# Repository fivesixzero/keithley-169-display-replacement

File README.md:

# Keithley 169 Multimeter Display Replacement

KiCad files, images, and documentation for replacing the Keithley 169's original LCD panel.

Also includes selected historical data including ad clippings and datasheets about the circa 1979 Keithley 169 digital multimeter and the Intersil ICL-7106R chip its built around.

## Overview

Many aging Keithley 169 multimeters have displays that are broken or flooded with liquid crystal. Because of this, they end up being thrown away or are left to be used for parts. This makes me sad.

The the main purpose of this project is to replace the Keithley 169's 'unobtanium' custom LCD display part with something inexpensive and (ideally) widely available as of mid-2021. Even if the part(s) selected in this project are unavailable in the future, or if more appropriate parts become available, this project should provide a solid starting point for future related work.

The secondary objective of this project is to provide an excuse to learn KiCad and do some historical digging about late 1970's digital multimeters, with a focus on multimeters based on the ICL7106 and its various variants.

## What's In This Repo?

The KiCad files for the board's schematic, PCB layout, symbols, and part footprints along with manufacturing output Gerber files are in `board`.

Key part datasheets and other historical data, along with images from my own build, are under `images`.

## Historical Context

### Digital Multimeters in the 70's

Largely due to the cost, DMMs were pretty exotic tech, despite having been around since the mid 1950's. The benefits the DMM over the analog meter were vast though.

Portability was becoming a larger concern too, now that it wasn't just "men of science" in lab coats, factory workers on an assembly line, or military signals specialists that needed to keep an eye on electronics. Tradespeople like electricians, auto mechanics, and service techs repairing millions of TVs, radios, and appliances all needed a reliable tool for their work. Adding to this was a rapidly growing consumer market driven by DIY tinkers, auto enthusiasts, HAM and CB radio folks, and those weird "computer clubs" popping up in California and Texas and, by the late 70's, all over the place.

A few smart players, including leadership at the John Fluke Company, saw an opportunity and a potentially huge addressable market. The key barrier to breaking into and expanding this market was price. Sure, equipment had to be rugged, reliable, and accurate, but those were comparatively easy problems to solve. But at the end of the day, DMMs were an order of magnitude too costly.

### The Fluke 8020A

As the story goes, in the mid-70's Fluke began a project with LSI specialists at Intersil. Their goal? To create an LSI device that could allow for the creation of a low-cost, portable, accurate, low-power-draw digital multimeter. When Fluke/Intersil started their work DMMs were very much out of the reach of average people and even most tradespeople. Portable options existed but they were typically just heavy, bulky bench gear with handles that could be powered on for only a few hours on a single charge or set of disposable batteries. This project aimed to flip that on its head.

In mid 1977, the Fluke 8202A was born. The chip at the heart of the 8020A, the Fluke `429100`, was nothing short of revolutionary. It enabled the development of a futuristic device that could do everything most people needed and it was a fraction of the price at $169, or around $1050 in 2021-adjusted buying power. While this sounds expensive today it was a huge deal at the time and was arguably the first practical example of a whole new type of everyday tool - the handheld multimeter.

Not much later, in 1978, Intersil released their `ICL7106` and its LED-driving sibling the `ICL7107`. Word has it that when Fluke heard about this chip, their engineers picked one up and took a look under the hood, finding that it was the very same design they had worked on with Intersil - right down to a tiny Fluke logo on the circuit mask. In an apparent effort to differentiate the design, Intersil had masked over (removed) one key feature (an internal switch to increase the input voltage range form 200mV to 2V) but that wasn't enough to stop a lawsuit from Fluke.

### The Intersil `ICL7106`

Of course, given the close relationship and interdependency between the two companies that suit was short-lived and settled out of court. But the cat was out of the bag - the `ICL7106` was ready for prime time. By the end of 1978 the `7106` was being sold by electronics distributors in kit form for as little as $30, complete with a new high-tech LCD panel! All a hobbyist (or prototype developer) had to do was give it zero to 200mV and, boom, they could get a 3.5-digit readout.

The key innovation was the fact that the `ICL7106` combined two key things into a single package - a high quality, dual-slope ADC and a 7-segment decoder/display driver. Neither of two things were particularly new, but having them in a single package was a huge innovation. Two major, complex sub-circuits that used to require dozens of discrete components were almost entirely eliminated from the board!

### DMM Democratization

So it wasn't just hobbyists paying attention to this new chip. Just about every test gear maker had at least one `ICL710x` based product in the works by the end of 1978. All a designer had to do was make sure that an analog font-end could present the LSI with a properly conditioned/divided input voltage, add a few decent-quality capacitors and resistors, and wire up a display.

Before long every manufacturer of test equipment (and a few 'new' names) had portable DMMs on the market and prices plummeted. Only a few years before, an 3.5-digit DMM would've required an investment of $500+ and substantial real estate on a workbench. Now any engineer or tech could carry that capability in their pocket for under $200 with battery life measured in months and years.

By the middle of the 1980's decent quality DMMs could be found under $100 and, eventually, down into the $50 and lower price points that made them household items across the US. In the 90's, `ICL7106` successors, variants and clones brought prices down well under $10. And even today in 2021 you can still get `ICL7106`, its sibling chips like the `ICL7136` and `MAX130A`, and all kinds of pin-compatible clones from Digi-Key, Mouser, Farnell, TME, and dozens of AliExpress shops.

### Keithley in the 70's

Now lets go back to 1978. Looking in from the outside, it looks like Keithley's leadership saw an opportunity in the low-end market. Their expertise and reputation lay elsewhere, in building some of the highest-grade measurement gear in the world for government, institutions, and the most well-funded corporate R&D departments. But somewhere in the halls of Keithley's offices, it seems like someone took a look at the Fluke 8020A and said, "I bet we can do that better."

Keithley had been building DMMs for the workbench for awhile at this point. As early as 1972 they had the $325 (~$2100 in 2021) Keithley 167, a 3.5-digit 'handheld' probe that was basically a tiny LCD display on the back of a bulky probe with a thick cable running back to a brick of bench tool. Later that year, a similar device, the 190 came to market with a 5.5-digit Nixie display for only $750 - around $4000 in 2021 dollars.

By the end of 1976, Keithley had a low-end to mid-range lineup that included 3.5-digit DMMs like the LCD-display 168 ($315) and 165 ($495), the 160B, and the 616 along with 4.5-digit DMMs like the 172 ($499) and 173 ($625), 171, 174, and 180. On the high end they had the 190 5.5-digit DMM. At the very top end, they had the 5900 and 6900, with "accuracy, stability, and sensitivity measured in ppm" and (likely) astronomical cost to go with it.

As the market accelerated toward the end of the 70's and LCD displays fully replaced Nixies, Keithley seems to have committed fully to the 'low end' of the market. Their 1978 lineup of all-LCD-display models was as strong as any other test gear company at the time. The model 179 was an LCD-display 4.5 digit meter for only $199, albeit with a few limitations. The 179 added a few things now considered critical, like sensitive TRMS AC measurements, at $289. Their more feature rich sibling, the 177, was quite a bit more capable but came in at a much higher price of $389. Then there was the 5.5-digit 191 at $499, complete with 4-wire resistance measurement - the cream of the 1978 crop.

So while they were certainly making strong moves in the low-cost corners of the market, even getting as low as $200, these were pretty pricey compared to their contemporaries. Their most inexpensive models often came with undesirable limitations. Battery power was an expensive option or aftermarket feature that could only offer a few dozen hours of battery life at best. And, most importantly, the 8020A hadn't come out yet.

### The Keithley 169

Enter the model 169, at $149.

Based on contextual data, like the frequency of ads and periodicals targeted by those ads, it looks like the Keithley 169 was announced in mid 1979 and started becoming available in quantity toward the end of that same year. This puts it squarely in the first or second generation of affordable meters based on the `ICL7106` chip.

Like most of the other brand-new 3.5-digit multimeters of the era, its specs were pretty impressive at the price. To differentiate the 169 from the others in its class, Keithley appears to have differentiated this meter with three main points.

First, it was portable. Not 8020A-style handheld portable, but portable via a pretty well engineered handle on a case the size of a large encyclopedia book. More impressive was the 1 year of battery life on a fresh set of 6 "C" batteries, co-incidentally the recommend time between calibrations.

Second, it was rugged. They touted the ruggedized thermoplastic, heavy input protection (1400V!), an MTBF of "20,000 hrs. or about 10 years", and "extensive vibration stress testing".

Third, Keithley was proud of its user interface. The display was "60% larger than other DMMs". It featured auto-zero, auto-polarity, and "color-coded front panel" that, at least in Keithley's eyes, was superior to their competition.

But most importantly, the price was $149, $20 cheaper than Fluke's 8020A.

Like a lot of things from the late 70's though, the 169 didn't live very long. Advertisements for the 169 only appear to have been published during a small window - from August of 1979 to March of 1980, or as late as June 1980 if you count an ad shared with the 130.

So by the time the 80's really started the 169 was already obsolete. On the low-end the industry as a whole abandoned the 'bench box' form-factor the 169 came in, replacing it with shirt-pocket-portable models. For Keithley, this was 130 family with the 130 at $99-115, the 131 at $134, the bringing-the-beeps-back 128 at $139, and the fanciest one, the 4.5-digit 135 at $219.

In the familiar bench-box format, the 169 was as low as Keithley ever got. In 1981 the 176 4.5-digit LCD DMM came in at a respectable $269. And with that, by 1982, the 169 looks like it was well and truly dead, at least in terms of marketing.

### Okay, so why fix up a Keithley 169?

I don't really have a single good answer for that. In many ways, its kind of a short-lived runt of the very large litter of late-70's DMMs. Its not particularly interesting in terms of specs, design, or historical importance. Its just another `ICL7106` follow-on of the historic 8020A, right?

Maybe. But for me, what sets this meter apart from the others is the engineering knowledge that went into building a stable and accurate analog front-end while also massively driving down the overall cost by keeping the design as simple as possible.

More speculatively, its possible that the 169 was effectively a prototype of sorts for the much more portable (and apparently more successful) follow-ups like the 130, 128, 131, and 135.

Either way, it played a part in bringing higher-quality measurement to the masses. And that's something I'll always find appealing.

### References

* George Rostky via EETimes, "Gauging the impact of DVMs", <https://web.archive.org/web/20040518004613/https://www.eet.com/anniversary/designclassics/gauging.html>
* `drtaylor` via EEVBlog forums, "History of the Fluke 8020A", <https://web.archive.org/web/20210301172454/https://www.eevblog.com/forum/testgear/history-of-the-fluke-8020-series/>
* Fluke, "Multimeter History", <https://www.fluke.com/en-us/learn/blog/digital-multimeters/multimeter-history>
* FundingUniverse, "Keithley Instruments History", <http://www.fundinguniverse.com/company-histories/keithley-instruments-inc-history/>

## License Clarifications

The license outlined in the `LICENSE` file in this repo is only relevant for the board files under `board`, the images under `images/k169-sn-59894` and `images/board`, and any Markdown documentation.

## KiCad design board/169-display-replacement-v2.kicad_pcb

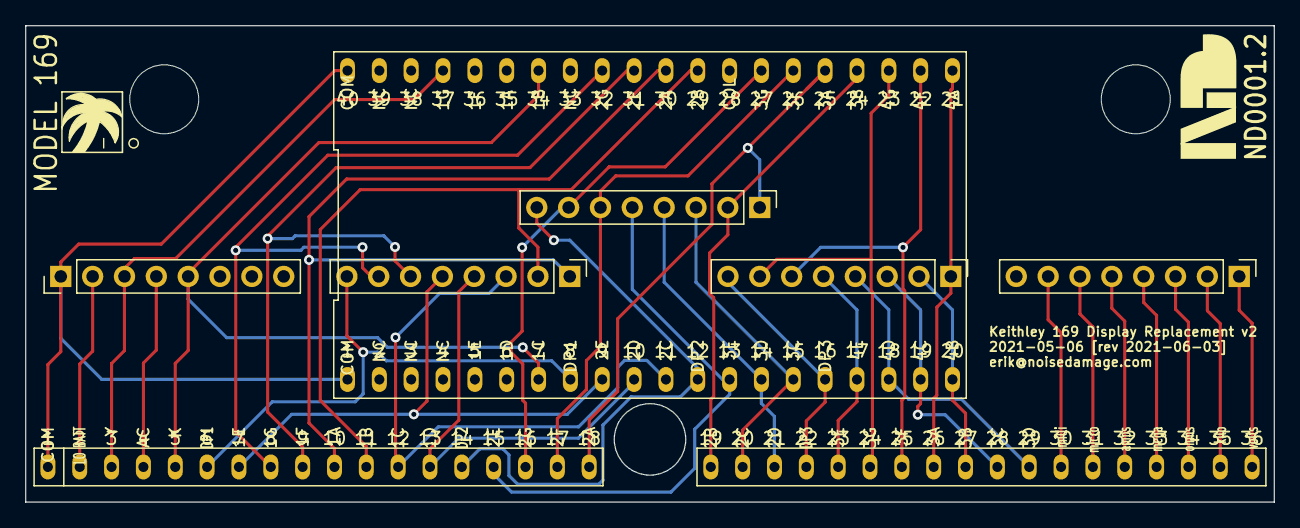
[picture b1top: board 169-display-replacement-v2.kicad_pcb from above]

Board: 2 copper layers, 99.6 x 38.0 mm, 7 parts (0 on the bottom side), 36 nets.

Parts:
J1: K169_LCD_Headers; K169_LCD_Header_narrow
J2: Util; PinHeader_1x08_P2.54mm_Vertical
J3: Dig1; PinHeader_1x08_P2.54mm_Vertical
J4: Dig2; PinHeader_1x08_P2.54mm_Vertical
J5: Dig3; PinHeader_1x08_P2.54mm_Vertical
J6: An; PinHeader_1x08_P2.54mm_Vertical
U1: LCD-A3X1C50TR/A; LCD-A3X1C50TR

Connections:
/1A: J1.10, J3.1, U1.30
/1B: J1.11, J3.2, U1.29
/1C: J1.12, J3.3, U1.11
/1D: J1.13, J3.4, U1.10
/1E: J1.7, J3.5, U1.9
/1F: J1.9, J3.6, U1.31
/1G: J1.8, J3.7, U1.32
/2A: J1.18, J4.1, U1.25
/2B: J1.19, J4.2, U1.24
/2C: J1.20, J4.3, U1.15
/2D: J1.21, J4.4, U1.14
/2E: J1.15, J4.5, U1.13
/2F: J1.17, J4.6, U1.26
/2G: J1.16, J4.7, U1.27
/3A: J1.26, J5.1, U1.21
/3B: J1.27, J5.2, U1.20
/3C: J1.28, J5.3, U1.19
/3D: J1.29, J5.4, U1.18
/3E: J1.23, J5.5, U1.17
/3F: J1.25, J5.6, U1.22
/3G: J1.24, J5.7, U1.23
/AC: J1.4, J2.4
/COM: J1.1, J2.1, U1.1, U1.40
/DP1: J1.6, J3.8, U1.8
/DP2: J1.14, J4.8, U1.12
/DP3: J1.22, J5.8, U1.16
/K: J1.5, J2.5, U1.7, U1.34
/LO_BATT: J1.2, J2.2
/Y: J1.3, J2.3, U1.37
/amps: J1.32, J6.5
/kilo: J1.35, J6.2
/mega: J1.33, J6.4
/micro: J1.31, J6.6
/milli: J1.30, J6.7
/ohms: J1.34, J6.3
/volts: J1.36, J6.1

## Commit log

2021-06-16 Adding .DS_Store to .gitignore
2021-06-16 Initial commit for KiCad and Gerber board data
2021-06-16 Initial commit for board imgaes
2021-06-16 Images from K169 sn 59894 repair
2021-06-16 Initial commit for readme.md including project overview and historical info
2021-06-16 Initial commit for datasheets and historical images/clips
2021-06-16 Adding image of LSI from sn59894, Intersil ITS80041, datecode 7937
2022-02-03 Adding image to readme
